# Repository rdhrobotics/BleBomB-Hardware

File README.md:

# BleBomB

**BleBomB** is a compact embedded device designed to generate **2.4 GHz noise** using an **NRF24 module** and the **MM32G0001A1T MCU**.

The device continuously transmits randomized packets in the 2.4 GHz band, which can create heavy interference for nearby wireless communications operating on the same frequency range.

## Overview

BleBomB is a fully embedded hardware project developed by **RDH Roboticss**.
This repository contains all the necessary **hardware design files** required to reproduce the device.

The system is built around a low-power microcontroller and a 2.4 GHz RF transceiver to produce rapid wireless transmissions.

## Hardware Components

* **MM32G0001A1T** Microcontroller
* **NRF24L01+** 2.4 GHz RF Transceiver
* Embedded PCB Design

## Features

* Compact embedded design
* Generates 2.4 GHz RF noise using NRF24 transmissions
* Low-power MCU control
* Open hardware design files included

## Repository Contents

This repository includes:

* **KiCad project files**
* **PCB layout**
* **Schematic diagrams**
* **Gerber files** for PCB manufacturing
* Hardware source files

## Development

The hardware was designed using **KiCad** and optimized for a small embedded form factor.

## Disclaimer

This project is intended **for educational and research purposes only**.
Users are responsible for ensuring compliance with their **local laws and regulations regarding RF transmissions**.

## Author

Developed by **RDH Roboticss**

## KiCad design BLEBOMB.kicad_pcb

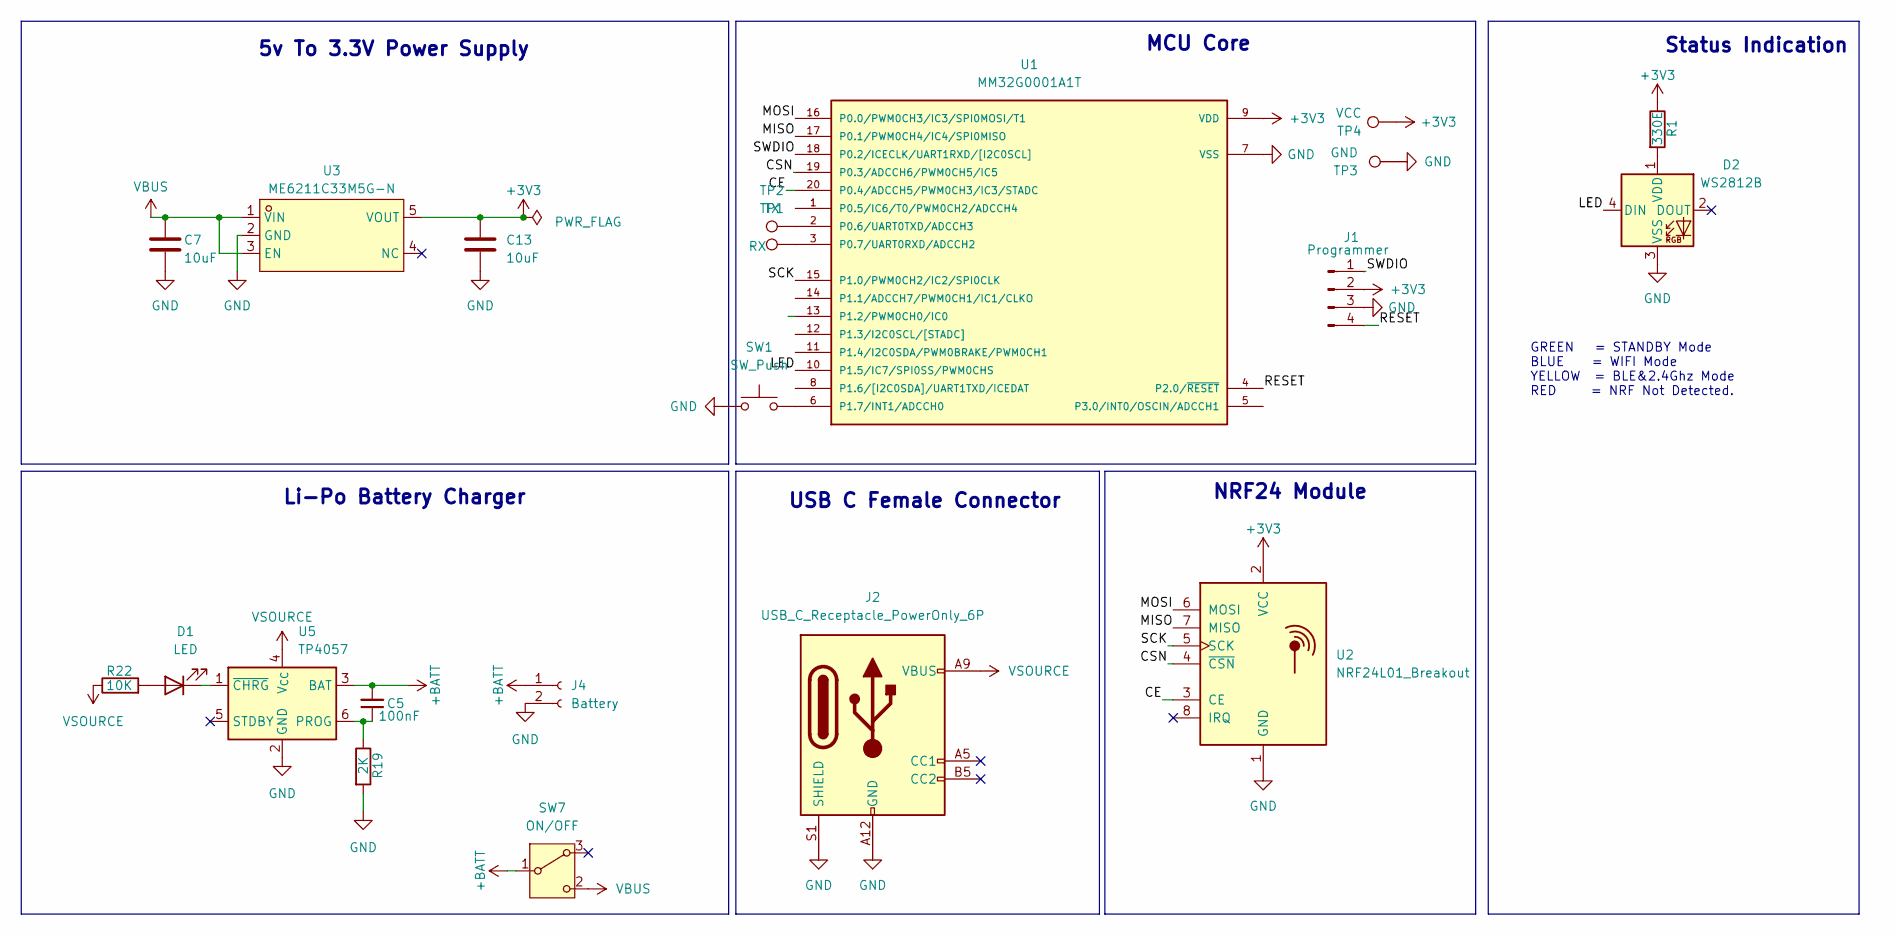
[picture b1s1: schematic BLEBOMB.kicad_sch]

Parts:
C5: 100nF; C_0805_2012Metric_Pad1.18x1.45mm_HandSolder
C7, C13: 10uF; C_0805_2012Metric_Pad1.18x1.45mm_HandSolder
D1: LED; LED_1206_3216Metric_Pad1.42x1.75mm_HandSolder
D2: WS2812B; LED_WS2812B_PLCC4_5.0x5.0mm_P3.2mm
J1: Programmer; PinSocket_1x04_P2.54mm_Vertical
J2: USB_C_Receptacle_PowerOnly_6P; USB_C_Receptacle_GCT_USB4125-xx-x_6P_TopMnt_Horizontal
J4: Battery; JST_PH_B2B-PH-K_1x02_P2.00mm_Vertical
R1: 330E; R_0805_2012Metric_Pad1.20x1.40mm_HandSolder
R19: 2K; R_0805_2012Metric_Pad1.20x1.40mm_HandSolder
R22: 10K; R_0805_2012Metric_Pad1.20x1.40mm_HandSolder
SW1: SW_Push; SW_SPST_TS-1088-xR020
SW7: ON/OFF; SW_SPDT_PCM12
TP1: RX; TestPoint_Pad_D1.0mm
TP2: TX; TestPoint_Pad_D1.0mm
TP3: GND; TestPoint_Pad_D1.0mm
TP4: VCC; TestPoint_Pad_D1.0mm
U1: MM32G0001A1T; TSSOP20
U2: NRF24L01_Breakout; nRF24L01_Breakout
U3: ME6211C33M5G-N; SOT-23-5_HandSoldering; MPN C82942
U5: TP4057; TSOT-23-6

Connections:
+3V3: C13.1, J1.2, R1.1, TP4.1, U1.9 (VDD), U2.2 (VCC), U3.5 (VOUT)
+BATT: C5.2, J4.1, SW7.1 (B), U5.3 (BAT)
/CE: U1.20 (P0.4/ADCCH5/PWM0CH3/IC3/STADC), U2.3 (CE)
/CSN: U1.19 (P0.3/ADCCH6/PWM0CH5/IC5), U2.4 (~CSN)
/LED: D2.4 (DIN), U1.10 (P1.5/IC7/SPI0SS/PWM0CHS)
/MISO: U1.17 (P0.1/PWM0CH4/IC4/SPI0MISO), U2.7 (MISO)
/MOSI: U1.16 (P0.0/PWM0CH3/IC3/SPI0MOSI/T1), U2.6 (MOSI)
/RESET: J1.4, U1.4 (P2.0/~RESET)
/SCK: U1.15 (P1.0/PWM0CH2/IC2/SPI0CLK), U2.5 (SCK)
/SWDIO: J1.1, U1.18 (P0.2/ICECLK/UART1RXD/[I2C0SCL])
GND: C7.1, C13.2, D2.3 (VSS), J1.3, J2.A12 (GND), J2.B12 (GND), J2.S1 (SHIELD), J4.2, R19.2, SW1.1, TP3.1, U1.7 (VSS), U2.1 (GND), U3.2 (GND), U5.2 (GND)
unnamed: D1.2 (A), R22.2
unnamed: D1.1 (K), U5.1 (~CHRG)
unnamed: D2.1 (VDD), R1.2
unnamed: TP2.1, U1.2 (P0.6/UART0TXD/ADCCH3)
unnamed: TP1.1, U1.3 (P0.7/UART0RXD/ADCCH2)
unnamed: SW1.2, U1.6 (P1.7/INT1/ADCCH0)
unnamed: C5.1, R19.1, U5.6 (PROG)
VBUS: C7.2, SW7.2 (C), U3.1 (VIN), U3.3 (EN)
VSOURCE: J2.A9 (VBUS), J2.B9 (VBUS), R22.1, U5.4 (V_{CC})

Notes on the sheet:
5v To 3.3V Power Supply
USB C Female Connector
Status Indication
GREEN = STANDBY Mode BLUE = WIFI Mode YELLOW = BLE&2.4Ghz Mode RED = NRF Not Detected.
MCU Core
Li-Po Battery Charger
NRF24 Module

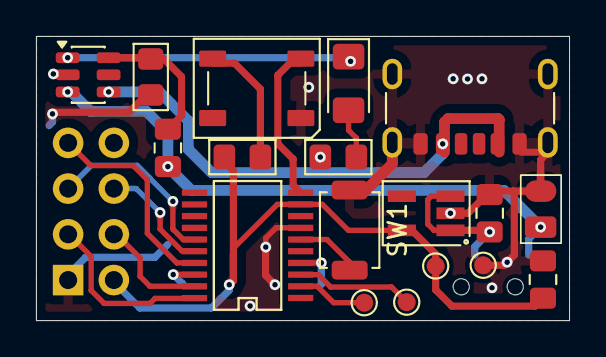
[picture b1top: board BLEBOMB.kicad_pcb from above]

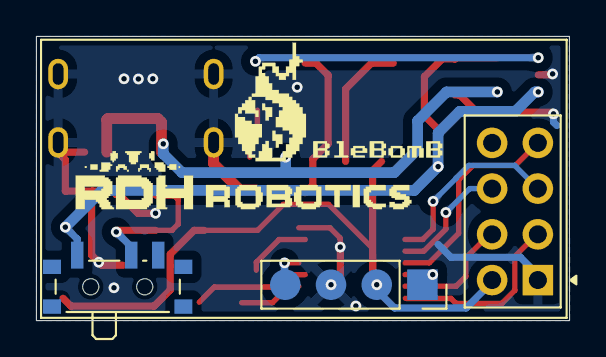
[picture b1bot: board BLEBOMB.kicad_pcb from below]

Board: 2 copper layers, 29.6 x 15.8 mm, 21 parts (3 on the bottom side), 20 nets.

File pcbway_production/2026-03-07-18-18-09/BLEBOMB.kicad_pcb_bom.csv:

Designator,Quantity,Value,Footprint,Package,MPN,DNP,Mount_Type,Description,Sim.Pins,MF,Description_1,Price,VALUE,SnapEDA_Link,MP,Availability,Check_prices
"C13, C7",2,10uF,C_0805_2012Metric_Pad1.18x1.45mm_HandSolder,,,,smt,,,,,,,,,,
C5,1,100nF,C_0805_2012Metric_Pad1.18x1.45mm_HandSolder,,,,smt,"Unpolarized capacitor, small symbol",,,,,,,,,
D1,1,LED,LED_1206_3216Metric_Pad1.42x1.75mm_HandSolder,,,,smt,Light emitting diode,1=K 2=A,,,,,,,,
D2,1,WS2812B,LED_WS2812B_PLCC4_5.0x5.0mm_P3.2mm,,,,smt,RGB LED with integrated controller,,,,,,,,,
J1,1,Programmer,PinSocket_1x04_P2.54mm_Vertical,,,,smt,"Generic connector, single row, 01x04, script generated",,,,,,,,,
J2,1,USB_C_Receptacle_PowerOnly_6P,USB_C_Receptacle_GCT_USB4125-xx-x_6P_TopMnt_Horizontal,,,,smt,USB Power-Only 6P Type-C Receptacle connector,,,,,,,,,
J4,1,Battery,JST_PH_B2B-PH-K_1x02_P2.00mm_Vertical,,,,tht,"Generic connector, single row, 01x02, script generated",,,,,,,,,
R1,1,330E,R_0805_2012Metric_Pad1.20x1.40mm_HandSolder,,,,smt,Resistor,,,,,,,,,
R19,1,2K,R_0805_2012Metric_Pad1.20x1.40mm_HandSolder,,,,smt,Resistor,,,,,,,,,
R22,1,10K,R_0805_2012Metric_Pad1.20x1.40mm_HandSolder,,,,smt,Resistor,,,,,,,,,
SW1,1,SW_Push,SW_SPST_TS-1088-xR020,,,,smt,"Push button switch, generic, two pins",,,,,,,,,
SW7,1,ON/OFF,SW_SPDT_PCM12,,,,smt,"Switch, single pole double throw",,,,,,,,,
TP1,1,RX,TestPoint_Pad_D1.0mm,,,,tht,test point,,,,,,,,,
TP2,1,TX,TestPoint_Pad_D1.0mm,,,,tht,test point,,,,,,,,,
TP3,1,GND,TestPoint_Pad_D1.0mm,,,,tht,test point,,,,,,,,,
TP4,1,VCC,TestPoint_Pad_D1.0mm,,,,tht,test point,,,,,,,,,
U1,1,MM32G0001A1T,TSSOP20,TSSOP-20 Nuvoton Technology,,,smt,,,Nuvoton Technology,8051 NuMicro MS51 Microcontroller IC 8-Bit 24MHz 16KB (16K x 8) FLASH 20-TSSOP,None,MS51FB9AE,https://www.snapeda.com/parts/MS51FB9AE/Nuvoton/view-part/?ref=snap,MS51FB9AE,In Stock,https://www.snapeda.com/parts/MS51FB9AE/Nuvoton/view-part/?ref=eda
U2,1,NRF24L01_Breakout,nRF24L01_Breakout,,,,tht,"Ultra low power 2.4GHz RF Transceiver, Carrier PCB",,,,,,,,,
U3,1,ME6211C33M5G-N,SOT-23-5_HandSoldering,,C82942,,smt,,,,,,,,,,
U5,1,TP4057,TSOT-23-6,,,,smt,"Constant-current/constant-voltage linear charger for single cell lithium-ion batteries with 2.9V Trickle Charge, 4.5V to 6.5V VDD, -40 to +85 degree Celsius, TSOT-23-6",,,,,,,,,

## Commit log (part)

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2026-03-07 Revise README for BleBomB project details
    Expanded the README to provide detailed information about the BleBomB project, including its purpose, components, features, and repository contents.
2026-03-07 Source Update
